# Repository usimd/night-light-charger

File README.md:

# Night light battery charger

One of our children's night light is battery-operated and does not feature a charging port but requires to open a battery enclosure and charge the batteries with an external charger.

This repo contains a small PCB project that adds a USB-C port for charging the three AA NiMH batteries using the [BQ25172](https://www.ti.com/lit/gpn/bq25172) charging IC. The charge current is adjustable using a potentiometer (up to the max. 800mA) and a dual color LED will indicate if the device is currently charging (red) and once charging has finished (green).

The PCB is fitted into the case of this ANSMANN device (https://shop.ansmann.de/en/cartoon-nachtlicht-maus).

## PCB design preview

This is a rendering of the board (missing a few models)

## Final implementation

The board fits suprisingly well into the case, I just had to remove maybe $\frac{2}{10} mm$ of the inner wall using a Dremel. Also the position of the USB-C connector is pretty well aligned with the outer wall. The dual LED intensity is strong enough to properly indicate the charging status.

Excuse my poor soldering skills, this is just to give you an impression:

</img> </img> </img> </img> </img> </img> 

## Want one, too?

I usually source parts for not just one unit. The PCB house also delivers at least three pieces as backups. 

If you'd also like to have one of these builds, open an issue in this repo. I will check if I have all parts and the PCB in stock and let you know how much it will cost. 
I have no intent to earn any money from these so I'll calculate the exact price based on my sourcing costs. 
If you're curious, I can share these details upon request in the process.

Payment needs to be done via GitHub sponsoring using a one-time donation. 

This project has been prototyped at [AISLER](https://aisler.net/p/OOQHJCJK).

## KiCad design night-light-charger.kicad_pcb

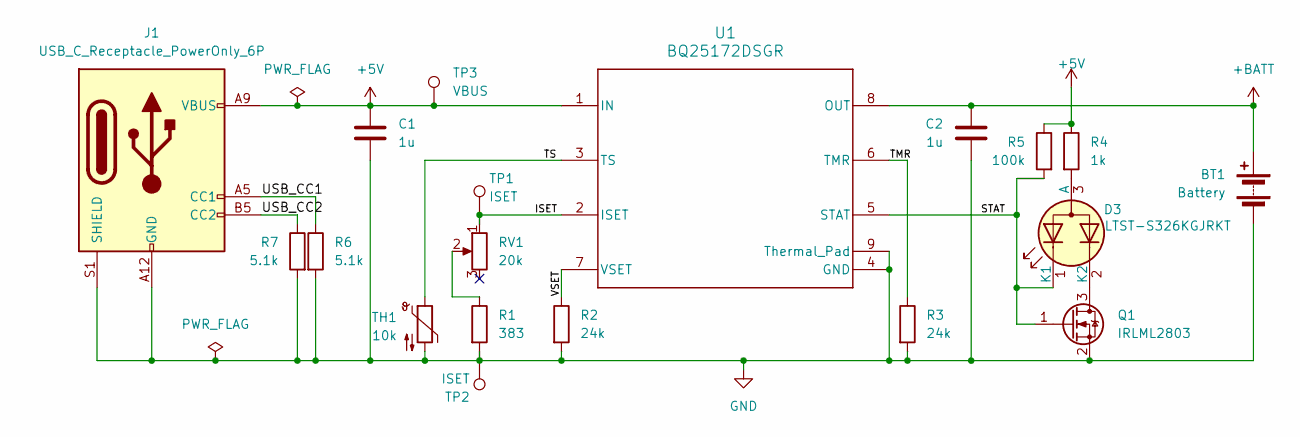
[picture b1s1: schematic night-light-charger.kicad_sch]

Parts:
BT1: Battery; PinHeader_1x02_P2.54mm_Vertical
C1, C2: 1u; C_0805_2012Metric
D3: LTST-S326KGJRKT; LED_LiteOn_LTST-S326; MPN LTST-S326KGJRKT
J1: USB_C_Receptacle_PowerOnly_6P; USB_C_Receptacle_G-Switch_GT-USB-7010ASV; MPN GT-USB-7010ASV
Q1: IRLML2803; SOT-23; MPN IRLML2803TRPBF
R1: 383; R_0603_1608Metric
R2, R3: 24k; R_0603_1608Metric
R4: 1k; R_0603_1608Metric
R5: 100k; R_0805_2012Metric
R6, R7: 5.1k; R_0402_1005Metric
RV1: 20k; Potentiometer_Bourns_3224W_Vertical; MPN 3224W-1-203E
TH1: 10k; R_Axial_DIN0204_L3.6mm_D1.6mm_P5.08mm_Vertical; MPN MF52A103J3435 (A1)
TP1, TP2: ISET; TestPoint_Pad_D1.0mm
TP3: VBUS; TestPoint_Pad_D1.0mm
U1: BQ25172DSGR; DSG0008A-IPC_A; MPN BQ25172DSGR

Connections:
+5V: C1.1, J1.A9 (VBUS), J1.B9 (VBUS), R4.1, R5.1, TP3.1, U1.1 (IN)
+BATT: BT1.1 (+), C2.1, U1.8 (OUT)
/ISET: RV1.1, TP1.1, U1.2 (ISET)
/STAT: D3.1 (K1), Q1.1 (G), R5.2, U1.5 (STAT)
/TMR: R3.1, U1.6 (TMR)
/TS: TH1.1, U1.3 (TS)
/USB_CC1: J1.A5 (CC1), R6.1
/USB_CC2: J1.B5 (CC2), R7.1
/VSET: R2.1, U1.7 (VSET)
GND: BT1.2 (-), C1.2, C2.2, J1.A12 (GND), J1.B12 (GND), J1.S1 (SHIELD), Q1.2 (S), R1.2, R2.2, R3.2, R6.2, R7.2, TH1.2, TP2.1, U1.4 (GND), U1.9 (Thermal_Pad)
unnamed: D3.3 (A), R4.2
unnamed: D3.2 (K2), Q1.3 (D)
unnamed: R1.1, RV1.2

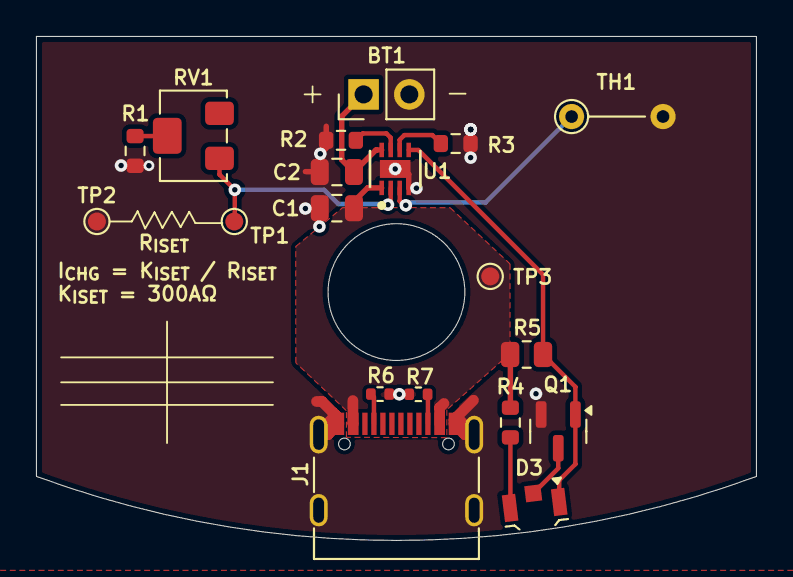
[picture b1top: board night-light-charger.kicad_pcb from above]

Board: 2 copper layers, 40.0 x 28.0 mm, 19 parts (0 on the bottom side), 13 nets.

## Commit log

2025-06-15 Import
2025-06-15 Add license
2025-10-17 Update part information
2025-10-29 Include information on how to request a build
    Added a section for users interested in obtaining a build.
